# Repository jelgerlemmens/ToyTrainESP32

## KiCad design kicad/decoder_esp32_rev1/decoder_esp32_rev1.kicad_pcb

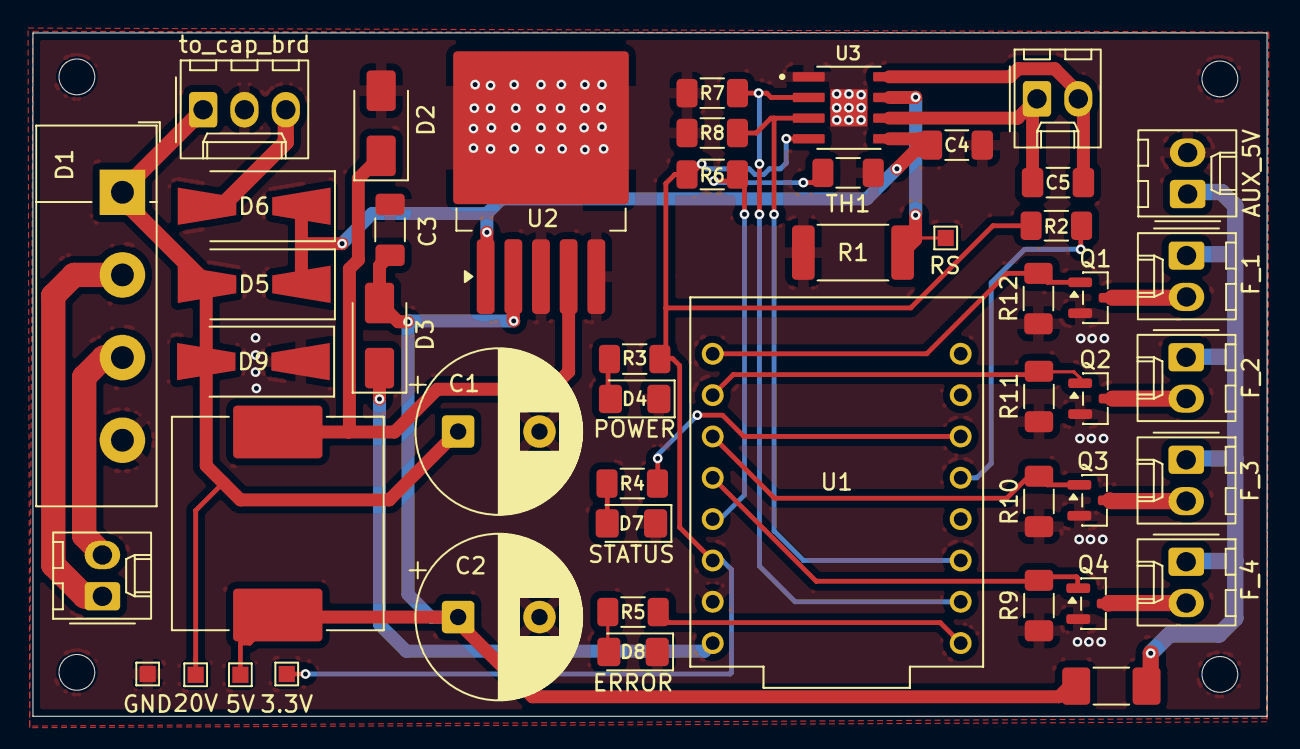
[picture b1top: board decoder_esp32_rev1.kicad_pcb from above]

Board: 2 copper layers, 75.9 x 42.0 mm, 49 parts (0 on the bottom side), 31 nets.

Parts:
C1: CP_Radial_D10.0mm_P5.00mm
C2: 470uF - 35V; CP_Radial_D10.0mm_P5.00mm
C3, C4, C5: 0.1uF; C_1206_3216Metric_Pad1.33x1.80mm_HandSolder
D1: KBU6B; Diode_Bridge_Vishay_KBU
D2, D3: SS34; D_SMA
D4: POWER; D_1206_3216Metric_Pad1.42x1.75mm_HandSolder
D5, D6: S5M; D_SMA-SMB_Universal_Handsoldering
D7: STATUS; D_1206_3216Metric_Pad1.42x1.75mm_HandSolder
D8: ERROR; D_1206_3216Metric_Pad1.42x1.75mm_HandSolder
D9: smbj24a; D_SMA-SMB_Universal_Handsoldering
F1: Fuse; C_1808_4520Metric_Pad1.72x2.30mm_HandSolder
J1: TRCK_IN; Molex_KK-254_AE-6410-02A_1x02_P2.54mm_Vertical
J2: F_2; Molex_KK-254_AE-6410-02A_1x02_P2.54mm_Vertical
J3: F_3; Molex_KK-254_AE-6410-02A_1x02_P2.54mm_Vertical
J4: F_1; Molex_KK-254_AE-6410-02A_1x02_P2.54mm_Vertical
J5: F_4; Molex_KK-254_AE-6410-02A_1x02_P2.54mm_Vertical
J6: AUX_5V; Molex_KK-254_AE-6410-02A_1x02_P2.54mm_Vertical
J8: MTR_OUT; Molex_KK-254_AE-6410-02A_1x02_P2.54mm_Vertical
J9: to_cap_brd; Molex_KK-254_AE-6410-03A_1x03_P2.54mm_Vertical
L1: 68uH; L_Changjiang_FXL1340
Q1, Q2, Q3, Q4: BSS138; SOT-23
R1: 0.15 Ohm; R_2512_6332Metric_Pad1.40x3.35mm_HandSolder
R2: 2.2K; R_1206_3216Metric_Pad1.30x1.75mm_HandSolder
R3: GRN 100Ohm; R_1206_3216Metric_Pad1.30x1.75mm_HandSolder
R4: Yellow Status 150Ohm; R_1206_3216Metric_Pad1.30x1.75mm_HandSolder
R5: Red ERROR 150Ohm; R_1206_3216Metric_Pad1.30x1.75mm_HandSolder
R6: 10k; R_1206_3216Metric_Pad1.30x1.75mm_HandSolder
R7, R8, R9, R10, R11, R12: 10K pulldown; R_1206_3216Metric_Pad1.30x1.75mm_HandSolder
TH1: Thermistor_NTC; R_1206_3216Metric_Pad1.30x1.75mm_HandSolder
TP1: GND; TestPoint_Pad_1.0x1.0mm
TP2: 20V; TestPoint_Pad_1.0x1.0mm
TP3: 5V; TestPoint_Pad_1.0x1.0mm
TP4: 3.3V; TestPoint_Pad_1.0x1.0mm
TP5: RS; TestPoint_Pad_1.0x1.0mm
U1: ESP32-C3_SUPERMINI_TH; MODULE_ESP32-C3_SUPERMINI_TH
U2: LM2596S-5; TO-263-5_TabPin3
U3: TB67H450FNG_EL; SOIC127P599X175-9N

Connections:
GND: C1.2, C2.2, C3.1, C4.1, D1.4 (-), D2.2 (A), D4.1 (K), D7.1 (K), D8.1 (K), D9.1 (K), J6.2, J9.2, Q1.2 (S), Q2.2 (S), Q3.2 (S), Q4.2 (S), R1.2, R7.1, R8.2, R9.1, R10.1, R11.1, R12.1, TH1.2, TP1.1 (1_1), U1.G (GND), U2.3 (GND), U2.5 (~ON/OFF), U3.1 (GND), U3.9 (GND)
unnamed: C1.1, D1.1 (+), D5.2 (A), D9.2 (A), J9.1, TP2.1 (1_1)
unnamed: D2.1 (K), L1.1, U2.4 (FB)
unnamed: C2.1, C3.2, D3.2 (A), F1.1, L1.2, TP3.1 (1_1), U2.2 (OUT)
unnamed: D3.1 (K), U1.5V
unnamed: D4.2 (A), R3.2
unnamed: C4.2, D5.1 (K), D6.1 (K), U2.1 (VIN), U3.5 (VM)
unnamed: D6.2 (A), J9.3
unnamed: D7.2 (A), R4.2
unnamed: D8.2 (A), R5.2
unnamed: D1.2, J1.1
unnamed: D1.3, J1.2
unnamed: F1.2, J2.1, J3.1, J4.1, J5.1, J6.1
unnamed: J2.2, Q2.3 (D)
unnamed: J3.2, Q3.3 (D)
unnamed: J4.2, Q1.3 (D)
unnamed: J5.2, Q4.3 (D)
unnamed: C5.1, J8.1, U3.6 (OUT1)
unnamed: C5.2, J8.2, U3.8 (OUT2)
unnamed: Q1.1 (G), R12.2, U1.0 (GPIO0)
unnamed: Q2.1 (G), R11.2, U1.1 (GPIO1)
unnamed: Q3.1 (G), R10.2, U1.2 (GPIO2)
unnamed: Q4.1 (G), R9.2, U1.3 (GPIO3)
unnamed: R2.2, R3.1, R6.1, TP4.1 (1_1), U1.3.3 (3V3), U3.4 (VREF)
unnamed: R6.2, TH1.1, U1.4 (GPIO4)
unnamed: R5.1, U1.5 (GPIO5)
unnamed: R7.2, U1.6 (GPIO6), U3.2 (IN2)
unnamed: R8.1, U1.7 (GPIO7), U3.3 (IN1)
unnamed: R2.1, U1.9 (GPIO9)
unnamed: R4.1, U1.10 (GPIO10)
unnamed: R1.1, TP5.1 (1_1), U3.7 (RS)
